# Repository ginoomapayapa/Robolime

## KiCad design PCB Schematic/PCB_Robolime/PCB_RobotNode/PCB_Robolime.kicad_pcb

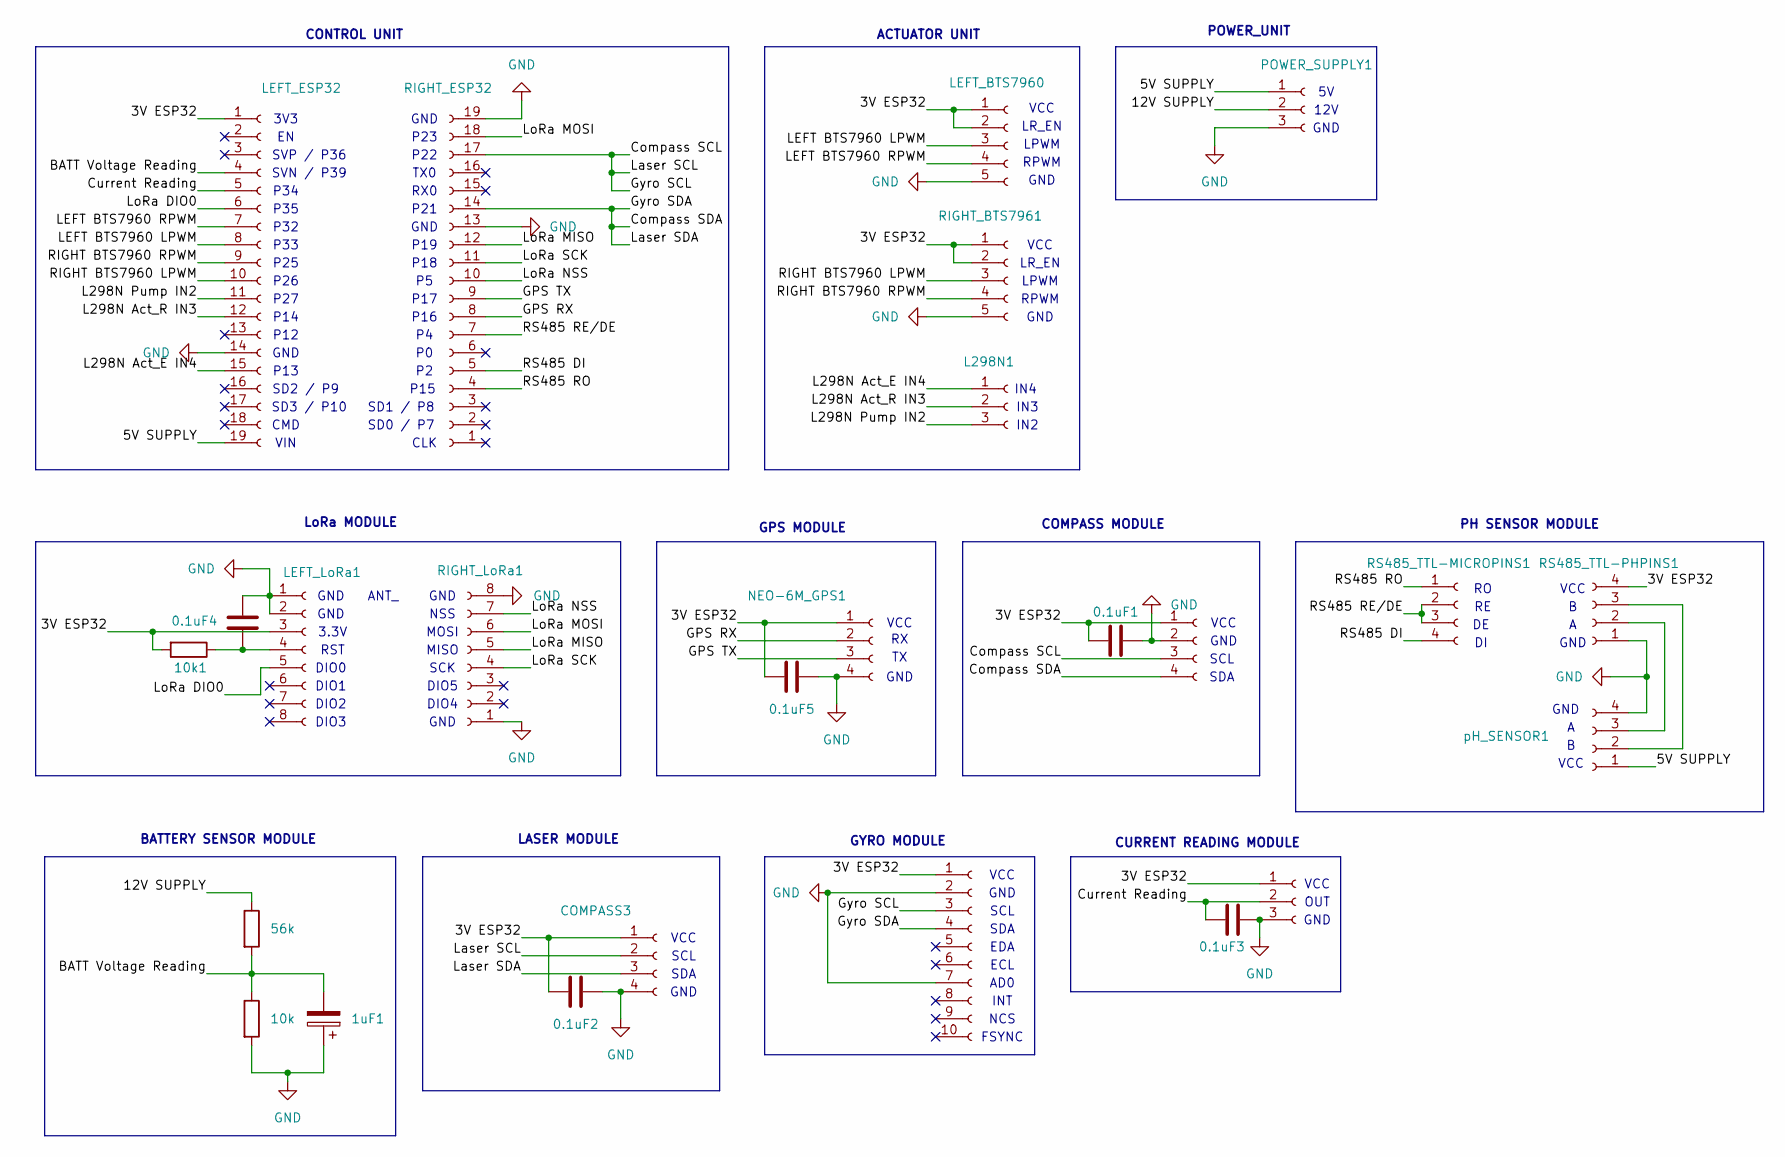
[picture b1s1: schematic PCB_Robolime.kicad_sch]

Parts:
0.1uF1, 0.1uF2, 0.1uF3, 0.1uF4, 0.1uF5: C; C_Disc_D3.0mm_W2.0mm_P2.50mm
1uF1: C_Polarized; CP_Radial_D5.0mm_P2.00mm
10k1: R; R_Axial_DIN0204_L3.6mm_D1.6mm_P7.62mm_Horizontal
COMPASS1: Conn_01x04_Socket; PinHeader_1x04_P2.54mm_Vertical
COMPASS3: Conn_01x04_Socket; JST_XH_B4B-XH-A_1x04_P2.50mm_Vertical
J1: Conn_01x10_Socket; PinHeader_1x10_P2.54mm_Vertical
J2: Conn_01x03_Socket; PinHeader_1x03_P2.54mm_Vertical
L298N1: Conn_01x03_Socket; JST_XH_B3B-XH-A_1x03_P2.50mm_Vertical
LEFT_BTS7960: Conn_01x05_Socket; JST_XH_B5B-XH-A_1x05_P2.50mm_Vertical
LEFT_ESP32: Conn_01x19_Socket; PinHeader_1x19_P2.54mm_Vertical
LEFT_LoRa1: Conn_01x08_Socket; PinHeader_1x08_P2.54mm_Vertical
NEO-6M_GPS1: Conn_01x04_Socket; JST_XH_B4B-XH-A_1x04_P2.50mm_Vertical
POWER_SUPPLY1: Conn_01x03_Socket; JST_XH_B3B-XH-A_1x03_P2.50mm_Vertical
R1: 56k; R_Axial_DIN0207_L6.3mm_D2.5mm_P7.62mm_Horizontal
R2: 10k; R_Axial_DIN0207_L6.3mm_D2.5mm_P7.62mm_Horizontal
RIGHT_BTS7961: Conn_01x05_Socket; JST_XH_B5B-XH-A_1x05_P2.50mm_Vertical
RIGHT_ESP32: Conn_01x19_Socket; PinHeader_1x19_P2.54mm_Vertical
RIGHT_LoRa1: Conn_01x08_Socket; PinHeader_1x08_P2.54mm_Vertical
RS485_TTL-MICROPINS1, RS485_TTL-PHPINS1: Conn_01x04_Socket; PinHeader_1x04_P2.54mm_Vertical
pH_SENSOR1: Conn_01x04_Socket; JST_XH_B4B-XH-A_1x04_P2.50mm_Vertical

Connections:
/3V ESP32: 0.1uF1.1, 0.1uF2.1, 0.1uF5.1, 10k1.2, COMPASS1.1, COMPASS3.1, J1.1, J2.1, LEFT_BTS7960.1, LEFT_BTS7960.2, LEFT_ESP32.1, LEFT_LoRa1.3, NEO-6M_GPS1.1, RIGHT_BTS7961.1, RIGHT_BTS7961.2, RS485_TTL-PHPINS1.4; also elsewhere on the board
/5V SUPPLY: LEFT_ESP32.19, POWER_SUPPLY1.1, pH_SENSOR1.1
/12V SUPPLY: POWER_SUPPLY1.2, R1.1
/BATT Voltage Reading: 1uF1.2, LEFT_ESP32.4, R1.2, R2.1
/Compass SCL: COMPASS1.3, COMPASS3.2, J1.3, RIGHT_ESP32.17; also elsewhere on the board
/Compass SDA: COMPASS1.4, COMPASS3.3, J1.4, RIGHT_ESP32.14; also elsewhere on the board
/Current Reading: 0.1uF3.1, J2.2, LEFT_ESP32.5
/GPS RX: NEO-6M_GPS1.2, RIGHT_ESP32.8
/GPS TX: NEO-6M_GPS1.3, RIGHT_ESP32.9
/L298N Act_E IN4: L298N1.1, LEFT_ESP32.15
/L298N Act_R IN3: L298N1.2, LEFT_ESP32.12
/L298N Pump IN2: L298N1.3, LEFT_ESP32.11
/LEFT BTS7960 LPWM: LEFT_BTS7960.3, LEFT_ESP32.8
/LEFT BTS7960 RPWM: LEFT_BTS7960.4, LEFT_ESP32.7
/LoRa DIO0: LEFT_ESP32.6, LEFT_LoRa1.5
/LoRa MISO: RIGHT_ESP32.12, RIGHT_LoRa1.5
/LoRa MOSI: RIGHT_ESP32.18, RIGHT_LoRa1.6
/LoRa NSS: RIGHT_ESP32.10, RIGHT_LoRa1.7
/LoRa SCK: RIGHT_ESP32.11, RIGHT_LoRa1.4
/RIGHT BTS7960 LPWM: LEFT_ESP32.10, RIGHT_BTS7961.3
/RIGHT BTS7960 RPWM: LEFT_ESP32.9, RIGHT_BTS7961.4
/RS485 DI: RIGHT_ESP32.5, RS485_TTL-MICROPINS1.4
/RS485 RE/DE: RIGHT_ESP32.7, RS485_TTL-MICROPINS1.2, RS485_TTL-MICROPINS1.3
/RS485 RO: RIGHT_ESP32.4, RS485_TTL-MICROPINS1.1
GND: 0.1uF1.2, 0.1uF2.2, 0.1uF3.2, 0.1uF4.2, 0.1uF5.2, 1uF1.1, COMPASS1.2, COMPASS3.4, J1.2, J1.7, J2.3, LEFT_BTS7960.5, LEFT_ESP32.14, LEFT_LoRa1.1, LEFT_LoRa1.2, NEO-6M_GPS1.4, POWER_SUPPLY1.3, R2.2, RIGHT_BTS7961.5, RIGHT_ESP32.13, RIGHT_ESP32.19, RIGHT_LoRa1.1, RIGHT_LoRa1.8, RS485_TTL-PHPINS1.1, pH_SENSOR1.4; also elsewhere on the board
unnamed: 0.1uF4.1, 10k1.1, LEFT_LoRa1.4
unnamed: RS485_TTL-PHPINS1.2, pH_SENSOR1.3
unnamed: RS485_TTL-PHPINS1.3, pH_SENSOR1.2

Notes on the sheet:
SDA
DIO3
LR_EN
P14
SCL
P17
SVN / P39
OUT
IN2
CLK
MOSI
MISO
SD1 / P8
RPWM
ECL
DIO5
P15
CONTROL UNIT
GND
CMD
BATTERY SENSOR MODULE
VCC
LASER MODULE
SCK
SD0 / P7
COMPASS MODULE
SD3 / P10
P22
P21
LPWM
3V3
ACTUATOR UNIT
P13
P34
DIO1
GYRO MODULE
P26
CURRENT READING MODULE
NSS
P19

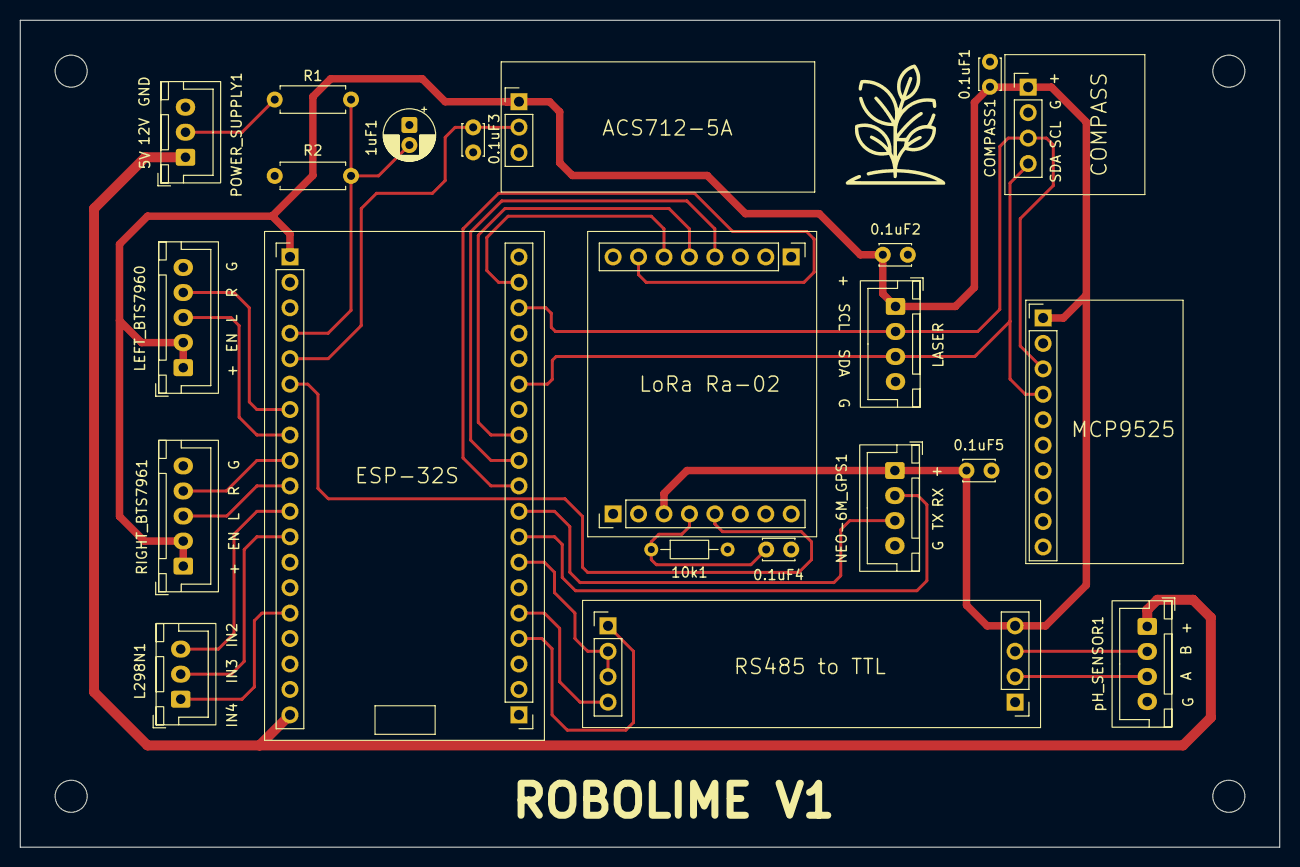
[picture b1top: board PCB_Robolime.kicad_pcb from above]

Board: 2 copper layers, 125.7 x 82.5 mm, 25 parts (0 on the bottom side), 28 nets.

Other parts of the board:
LASER: Conn_01x04_Socket; JST_XH_B4B-XH-A_1x04_P2.50mm_Vertical

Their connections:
/3V ESP32: LASER.1; also elsewhere on the board
/Compass SCL: LASER.2; also elsewhere on the board
/Compass SDA: LASER.3; also elsewhere on the board
GND: LASER.4; also elsewhere on the board

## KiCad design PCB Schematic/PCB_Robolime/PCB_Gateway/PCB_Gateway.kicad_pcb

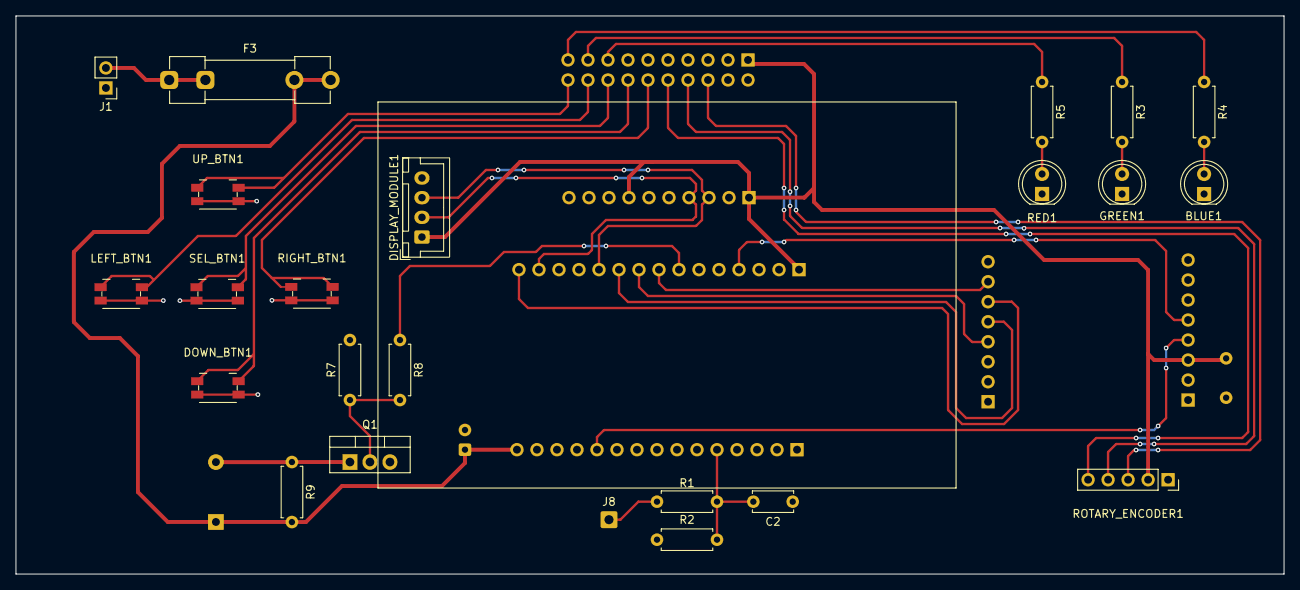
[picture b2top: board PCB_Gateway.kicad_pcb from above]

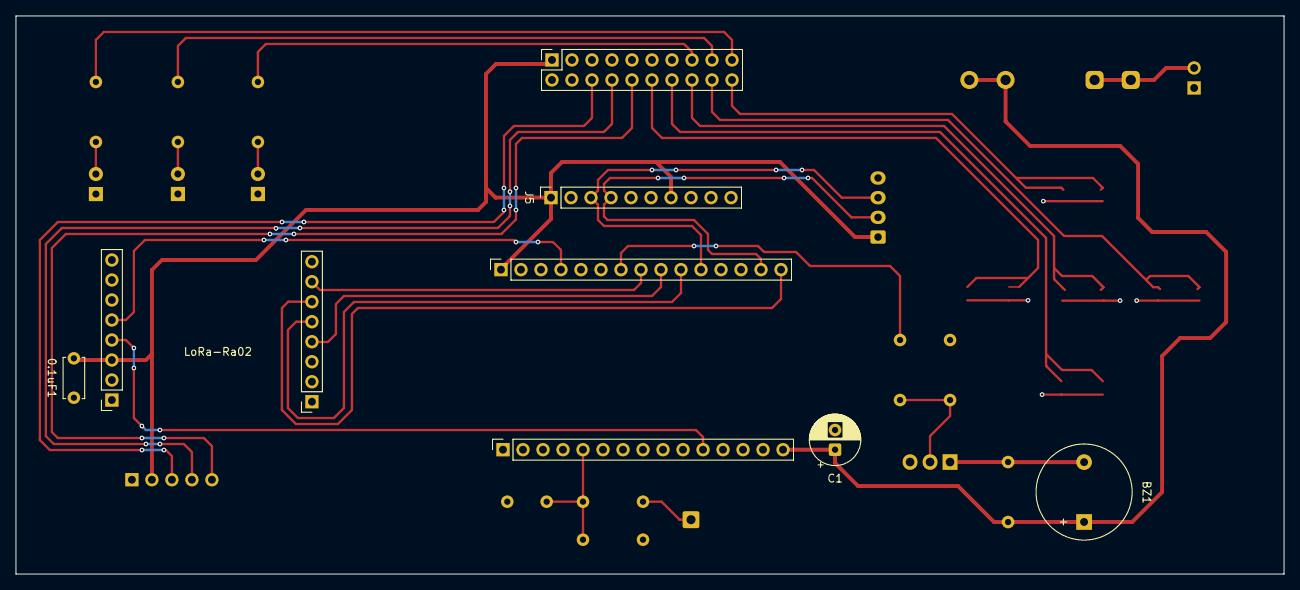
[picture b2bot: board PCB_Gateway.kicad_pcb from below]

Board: 2 copper layers, 161.0 x 70.9 mm, 32 parts (9 on the bottom side), 20 nets.

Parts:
0.1uF1: C_Small; C_Disc_D5.0mm_W2.5mm_P5.00mm
BLUE1: B_ACT; LED_D5.0mm
BZ1: Buzzer; Buzzer_12x9.5RM7.6
C1: 100uF; CP_Radial_D6.3mm_P2.50mm
C2: 0.1uF; C_Disc_D5.0mm_W2.5mm_P5.00mm
DISPLAY_MODULE1: Conn_01x04_Socket; JST_XH_B4B-XH-A_1x04_P2.50mm_Vertical
DOWN_BTN1: SW_Push; Panasonic_EVQPUJ_EVQPUA
ESP-32_DevkitV1: Conn_01x15_Socket; PinSocket_1x15_P2.54mm_Vertical
F3: 0.5A; Fuseholder_Clip-5x20mm_Littelfuse_100_Inline_P20.50x4.60mm_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
GREEN1: G_LoRa; LED_D5.0mm
J1: Conn_01x02_Socket; PinHeader_1x02_P2.54mm_Vertical
J2: Conn_01x15_Socket; PinSocket_1x15_P2.54mm_Vertical
J3: Conn_01x08_Socket; PinSocket_1x08_P2.54mm_Vertical
J4: DIN41612_02x10_AB; PinSocket_2x10_P2.54mm_Vertical
J5: Conn_01x10_Socket; PinSocket_1x10_P2.54mm_Vertical
J8: BATT_OUT; SolderWire-0.5sqmm_1x01_D0.9mm_OD2.1mm
LEFT_BTN1: SW_Push; Panasonic_EVQPUJ_EVQPUA
LoRa-Ra02: Conn_01x08_Socket; PinSocket_1x08_P2.54mm_Vertical
Q1: NPN; TO-220-3_Vertical
R1, R2: 100k; R_Axial_DIN0207_L6.3mm_D2.5mm_P7.62mm_Horizontal
R3, R4, R5: 330; R_Axial_DIN0207_L6.3mm_D2.5mm_P7.62mm_Horizontal
R7: 10k; R_Axial_DIN0207_L6.3mm_D2.5mm_P7.62mm_Horizontal
R8: 220; R_Axial_DIN0207_L6.3mm_D2.5mm_P7.62mm_Horizontal
R9: 1k; R_Axial_DIN0207_L6.3mm_D2.5mm_P7.62mm_Horizontal
RED1: R_ERROR; LED_D5.0mm
RIGHT_BTN1: SW_Push; Panasonic_EVQPUJ_EVQPUA
ROTARY_ENCODER1: Conn_01x05_Socket; PinSocket_1x05_P2.54mm_Vertical
SEL_BTN1: SW_Push; Panasonic_EVQPUJ_EVQPUA
UP_BTN1: SW_Push; Panasonic_EVQPUJ_EVQPUA

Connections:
/3V ESP32: 0.1uF1.1, DISPLAY_MODULE1.1, J2.1, J5.1, J5.7, LoRa-Ra02.3, ROTARY_ENCODER1.2
/5V: BZ1.1 (+), C1.1, ESP-32_DevkitV1.15, F3.2, R9.2
/BATT SENSOR: C2.1, ESP-32_DevkitV1.5, R1.2, R2.1
/BUZZER: J2.7, R8.1
/DISPLAY SCL: DISPLAY_MODULE1.3, J2.11, J5.3
/DISPLAY SDA: DISPLAY_MODULE1.2, J2.14, J5.4
/LoRa DIO0: J2.4, LoRa-Ra02.5
/LoRa MISO: J2.10, J3.5
/LoRa MOSI: J2.15, J3.6
/LoRa NSS: J2.8, J3.7
/LoRa RST: ESP-32_DevkitV1.11, LoRa-Ra02.4
/LoRa SCK: J2.9, J3.4
GND: 0.1uF1.2, BLUE1.1 (K), C1.2, C2.2, DISPLAY_MODULE1.4, DOWN_BTN1.2, GREEN1.1 (K), J1.1, J2.2, J3.8, J5.2, J5.8, J5.9, J5.10, LEFT_BTN1.2, LoRa-Ra02.1, LoRa-Ra02.2, Q1.3 (E), R2.2, R7.2, RED1.1 (K), RIGHT_BTN1.2, ROTARY_ENCODER1.1, SEL_BTN1.2, UP_BTN1.2
unnamed: BLUE1.2 (A), R4.2
unnamed: BZ1.2 (-), Q1.1 (C), R9.1
unnamed: GREEN1.2 (A), R3.2
unnamed: F3.1, J1.2
unnamed: J8.1 (Pin_1_1), R1.1
unnamed: Q1.2 (B), R7.1, R8.2
unnamed: R5.2, RED1.2 (A)
